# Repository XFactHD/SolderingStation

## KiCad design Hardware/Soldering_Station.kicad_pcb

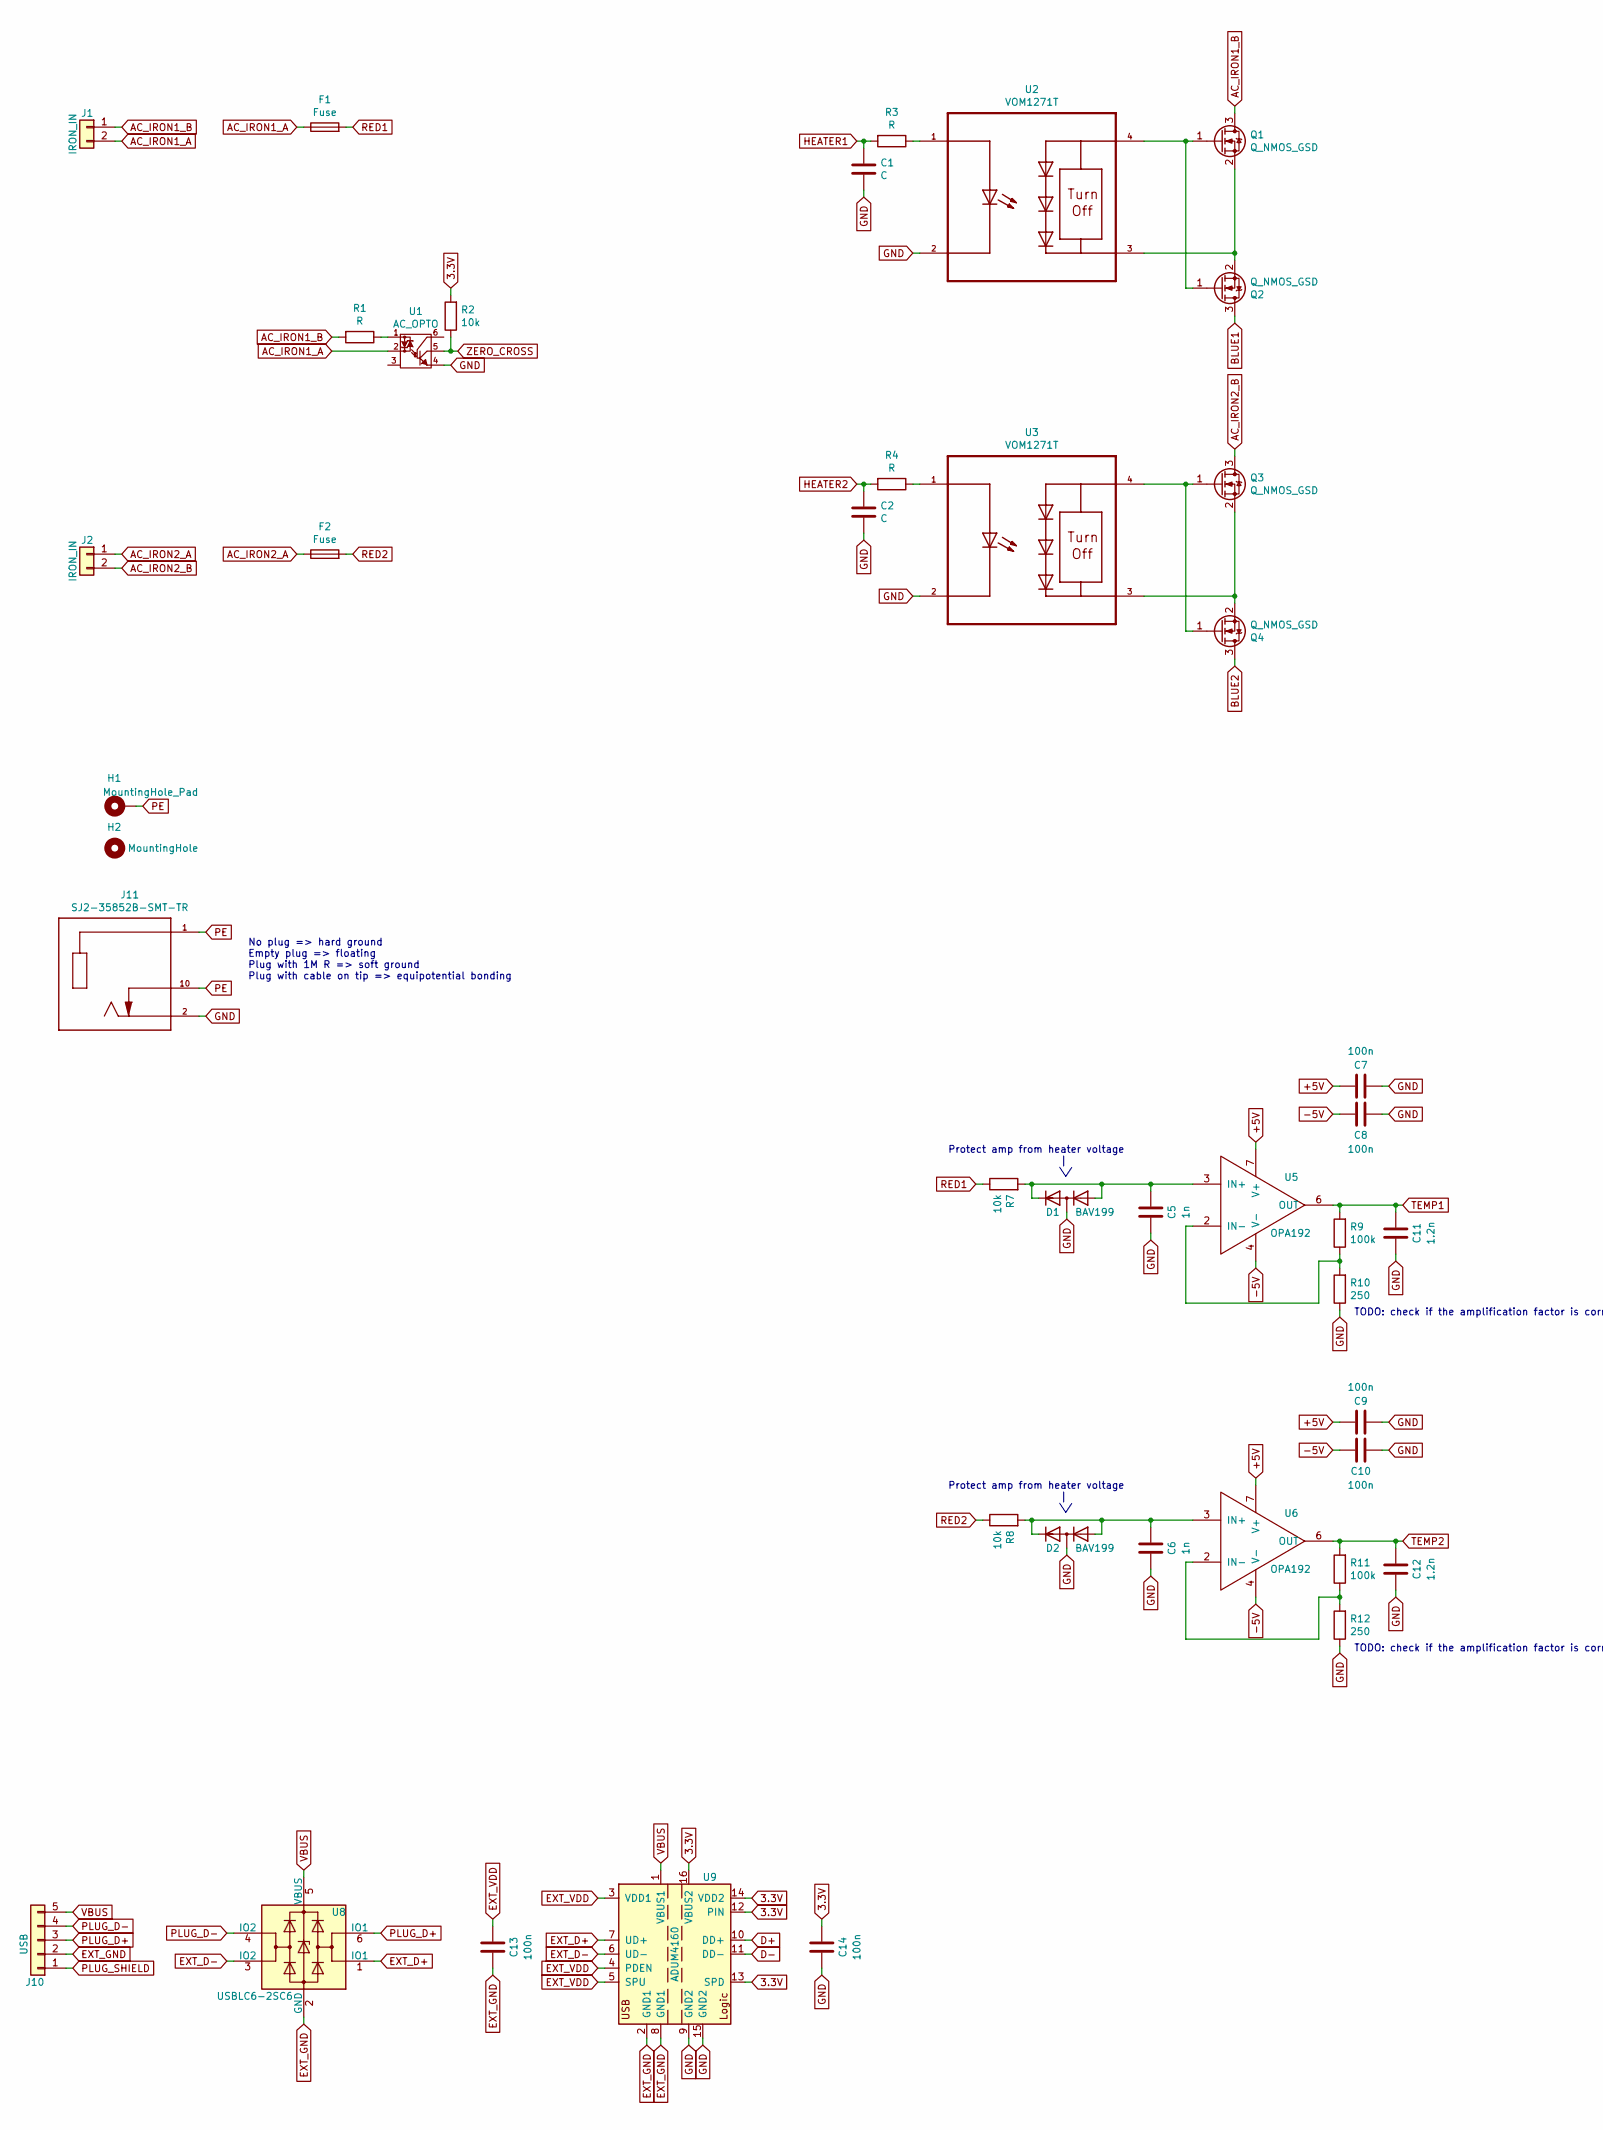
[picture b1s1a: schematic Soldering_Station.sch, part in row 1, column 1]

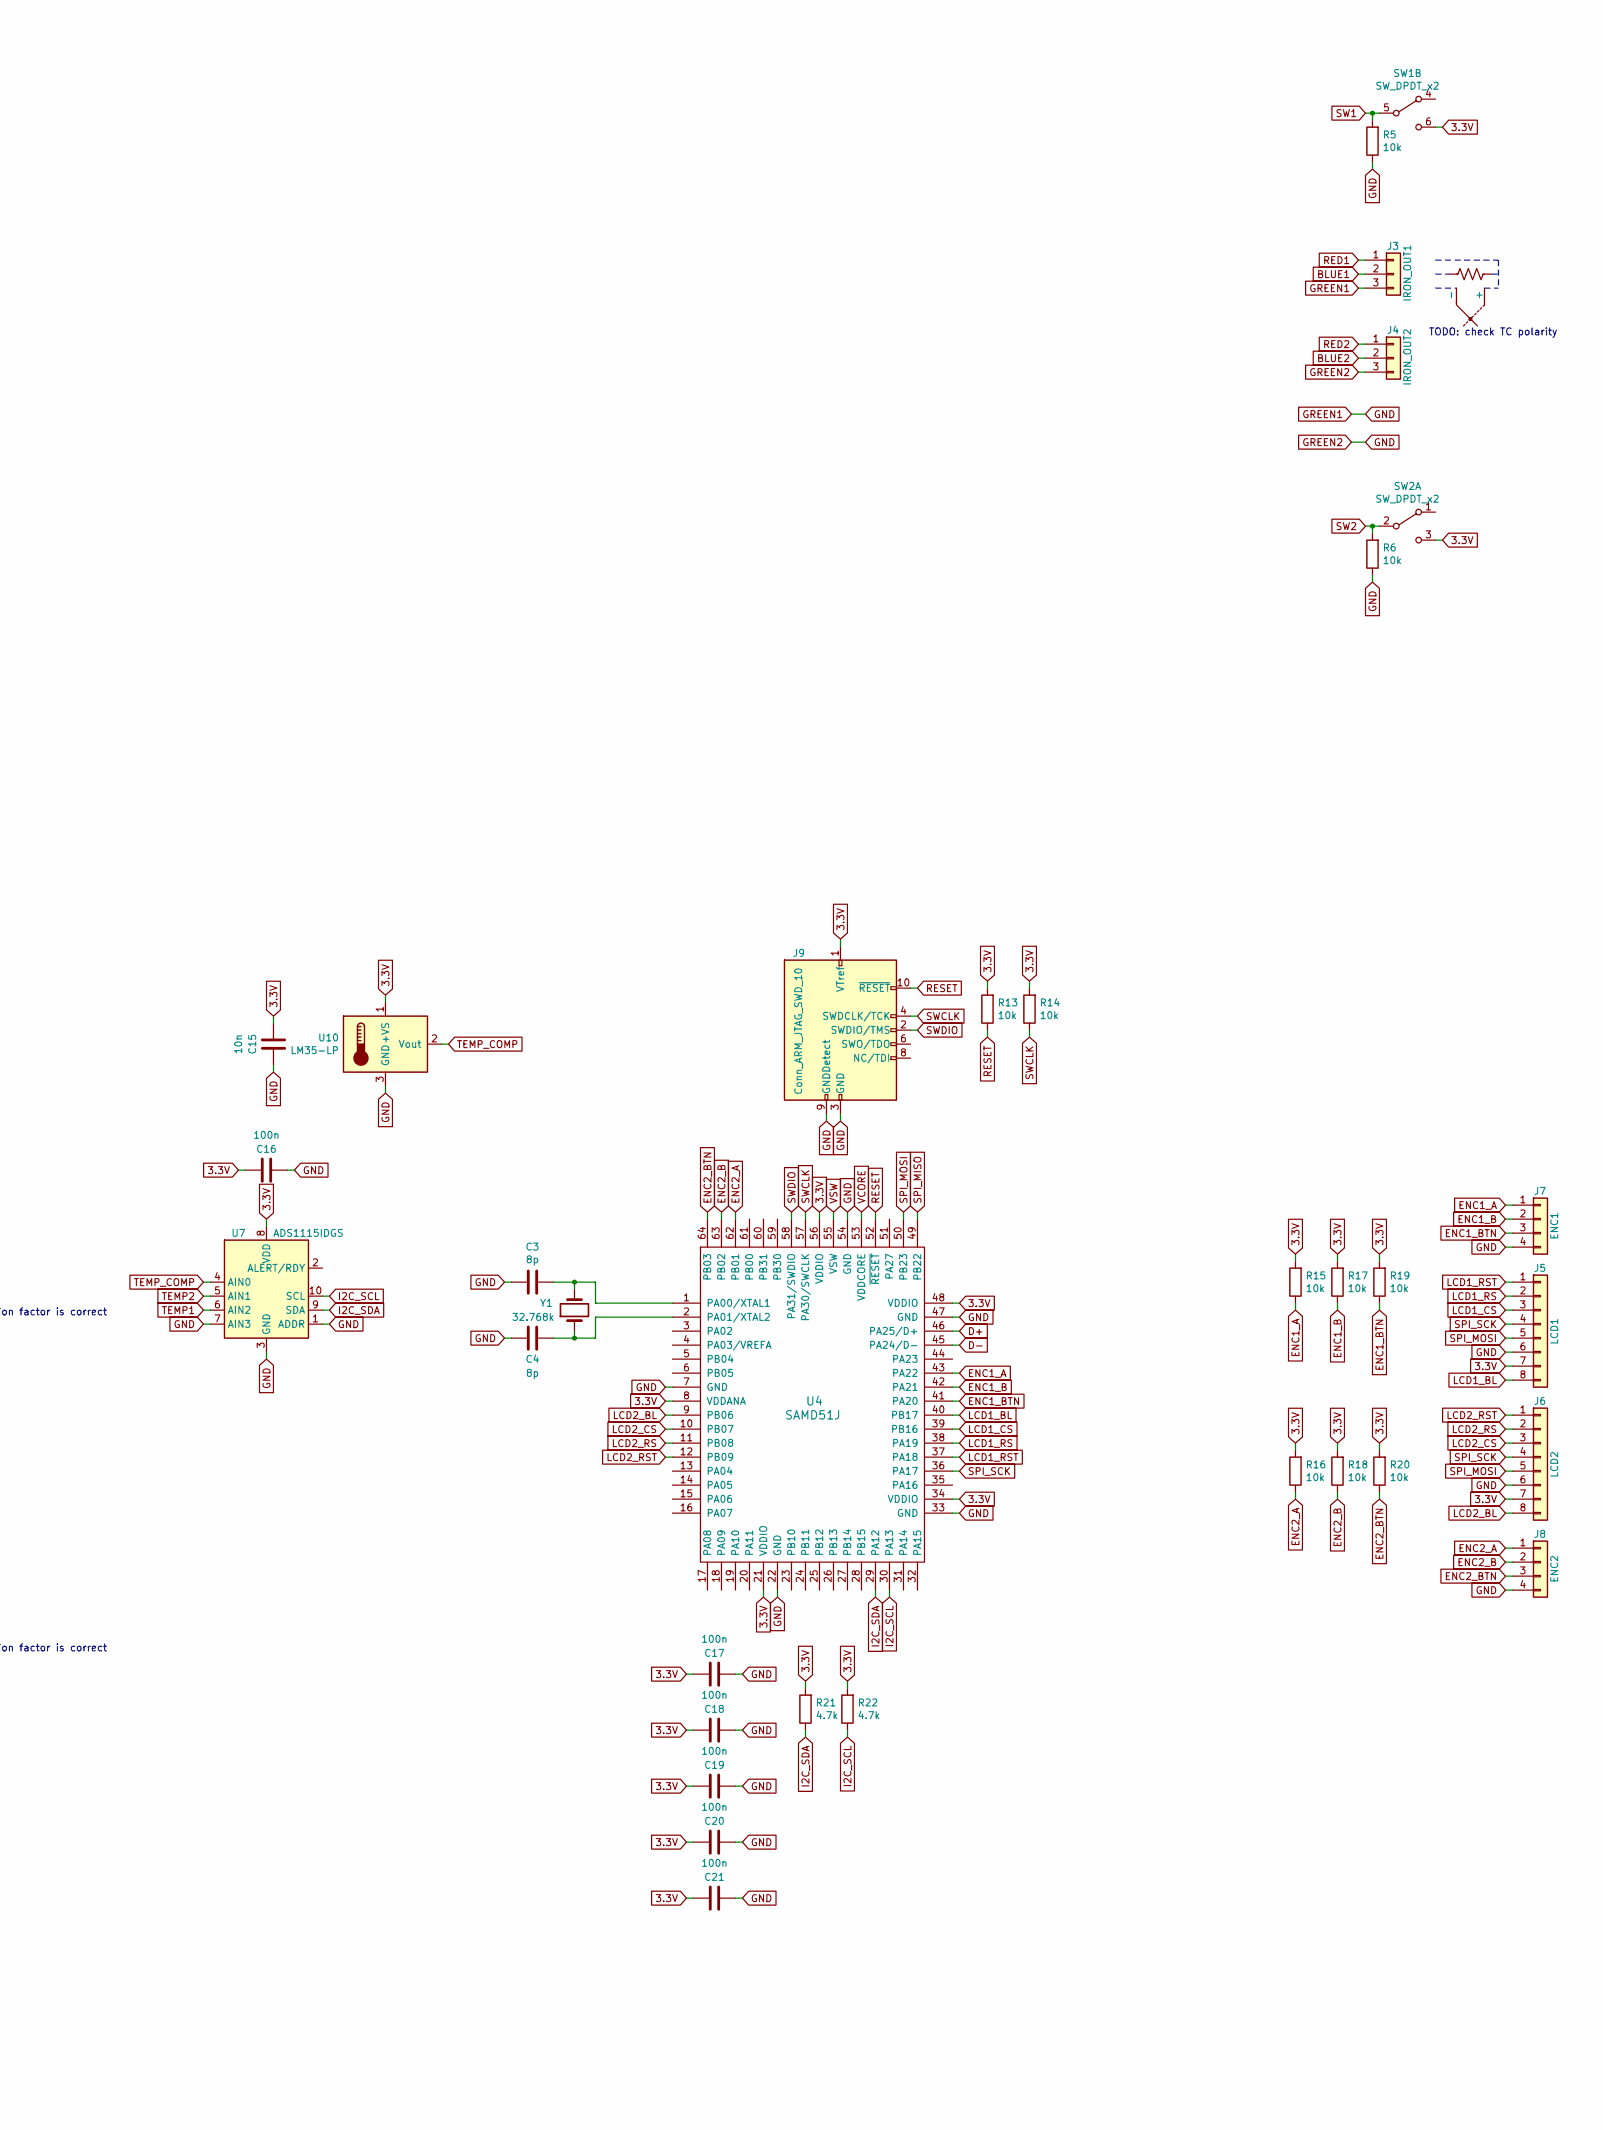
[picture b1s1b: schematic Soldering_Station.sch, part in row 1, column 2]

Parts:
C1, C2: C; C_0805
C3, C4: 8p; C_0805
C5, C6: 1n; C_0805
C7, C8, C9, C10, C13, C14, C16, C17, C18, C19, C20, C21: 100n; C_0805
C11, C12: 1.2n; C_0805
C15: 10n; C_0805
D1, D2: BAV199; SOT-23
F1, F2: Fuse; Fuseholder5x20_horiz_open_universal_Type-III
H1: MountingHole_Pad; 1pin
H2: MountingHole; 1pin
J1, J2: IRON_IN; PhoenixContact_MSTBVA-G_02x5.08mm_Vertical
J3: IRON_OUT1; PhoenixContact_MSTBVA-G_03x5.08mm_Vertical
J4: IRON_OUT2; PhoenixContact_MSTBVA-G_03x5.08mm_Vertical
J5: LCD1; JST_PH_B8B-PH-K_08x2.00mm_Straight
J6: LCD2; JST_PH_B8B-PH-K_08x2.00mm_Straight
J7: ENC1; JST_PH_B4B-PH-K_04x2.00mm_Straight
J8: ENC2; JST_PH_B4B-PH-K_04x2.00mm_Straight
J9: Conn_ARM_JTAG_SWD_10; Pin_Header_Straight_2x05_Pitch1.27mm
J10: USB; Pin_Header_Angled_1x05_Pitch2.54mm
J11: SJ2-35852B-SMT-TR; CUI_SJ2-35852B-SMT-TR
Q1, Q2, Q3, Q4: Q_NMOS_GSD; Infineon_PG-HSOF-8-1_ThermalVias
R1, R3, R4: R; R_0805
R2, R5, R6, R7, R8, R13, R14, R15, R16, R17, R18, R19, R20: 10k; R_0805
R9, R11: 100k; R_0805
R10, R12: 250; R_0805
R21, R22: 4.7k; R_0805
R130000: R_US
SW1, SW2: SW_DPDT_x2; NE182AEESNP6AMP
TC1: Thermocouple
U1: AC_OPTO; DIP-6_W7.62mm_SMDSocket_SmallPads
U2, U3: VOM1271T; SOP-4_3.8x4.1mm_Pitch2.54mm
U4: SAMD51J; TQFP-64_10x10mm_Pitch0.5mm
U5, U6: OPA192; SOIC-8_3.9x4.9mm_Pitch1.27mm
U7: ADS1115IDGS; TSSOP-10_3x3mm_Pitch0.5mm
U8: USBLC6-2SC6; SOT-23-6
U9: ADUM4160; SOIC-16W_7.5x10.3mm_Pitch1.27mm
U10: LM35-LP; TO-92_Inline_Narrow_Oval
Y1: 32.768k; Crystal_SMD_MicroCrystal_CC5V-T1A-2pin_4.1x1.5mm

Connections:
3.3V: C14.2, C15.1, C16.2, C17.2, C18.2, C19.2, C20.2, C21.2, J5.7, J6.7, J9.1 (VTref), R2.2, R13.2, R14.2, R15.2, R16.2, R17.2, R18.2, R19.2, R20.2, R21.2, R22.2, SW1.6 (C), SW2.3 (C), U4.8 (VDDANA), U4.21 (VDDIO), U4.34 (VDDIO), U4.48 (VDDIO), U4.56 (VDDIO), U7.8 (VDD), U9.12 (PIN), U9.13 (SPD), U9.14 (VDD2), U9.16 (VBUS2), U10.1 (+VS)
+5V: C7.2, C9.2, U5.7 (V+), U6.7 (V+)
-5V: C8.1, C10.1, U5.4 (V-), U6.4 (V-)
AC_IRON1_A: F1.1, J1.2, U1.2 (IN_2)
AC_IRON1_B: J1.1, Q1.3 (D), R1.2
AC_IRON2_A: F2.1, J2.1
AC_IRON2_B: J2.2, Q3.3 (D)
BLUE1: J3.2, Q2.3 (D)
BLUE2: J4.2, Q4.3 (D)
D+: U4.46 (PA25/D+), U9.10 (DD+)
D-: U4.45 (PA24/D-), U9.11 (DD-)
ENC1_A: J7.1, R15.1, U4.43 (PA22)
ENC1_B: J7.2, R17.1, U4.42 (PA21)
ENC1_BTN: J7.3, R19.1, U4.41 (PA20)
ENC2_A: J8.1, R16.1, U4.62 (PB01)
ENC2_B: J8.2, R18.1, U4.63 (PB02)
ENC2_BTN: J8.3, R20.1, U4.64 (PB03)
EXT_D+: U8.1 (IO1), U9.7 (UD+)
EXT_D-: U8.3 (IO2), U9.6 (UD-)
EXT_GND: C13.1, J10.2, U8.2 (GND), U9.2 (GND1), U9.8 (GND1)
EXT_VDD: C13.2, U9.3 (VDD1), U9.4 (PDEN), U9.5 (SPU)
GND: C1.2, C2.2, C3.1, C4.1, C5.1, C6.1, C7.1, C8.2, C9.1, C10.2, C11.1, C12.1, C14.1, C15.2, C16.1, C17.1, C18.1, C19.1, C20.1, C21.1, D1.3 (AC), D2.3 (AC), J3.3, J4.3, J5.6, J6.6, J7.4, J8.4, J9.3 (GND), J9.5 (GND), J9.9 (GNDDetect), J11.2 (TIP), R5.1, R6.1, R10.1, R12.1, U1.4 (E), U2.2 (C1), U3.2 (C1), U4.7 (GND), U4.22 (GND), U4.33 (GND), U4.47 (GND), U4.54 (GND), U7.1 (ADDR), U7.3 (GND), U7.7 (AIN3), U9.9 (GND2), U9.15 (GND2), U10.3 (GND)
HEATER1: C1.1, R3.2
HEATER2: C2.1, R4.2
I2C_SCL: R22.1, U4.30 (PA13), U7.10 (SCL)
I2C_SDA: R21.1, U4.29 (PA12), U7.9 (SDA)
LCD1_BL: J5.8, U4.40 (PB17)
LCD1_CS: J5.3, U4.39 (PB16)
LCD1_RS: J5.2, U4.38 (PA19)
LCD1_RST: J5.1, U4.37 (PA18)
LCD2_BL: J6.8, U4.9 (PB06)
LCD2_CS: J6.3, U4.10 (PB07)
LCD2_RS: J6.2, U4.11 (PB08)
LCD2_RST: J6.1, U4.12 (PB09)
unnamed: C3.2, U4.1 (PA00/XTAL1), Y1.2
unnamed: C4.2, U4.2 (PA01/XTAL2), Y1.1
unnamed: C5.2, D1.1 (A), D1.2 (C), R7.2, U5.3 (IN+)
unnamed: C6.2, D2.1 (A), D2.2 (C), R8.2, U6.3 (IN+)
unnamed: Q1.1 (G), Q2.1 (G), U2.4 (A2)
unnamed: Q1.2 (S), Q2.2 (S), U2.3 (C2)
unnamed: Q3.1 (G), Q4.1 (G), U3.4 (A2)
unnamed: Q3.2 (S), Q4.2 (S), U3.3 (C2)
unnamed: R1.1, U1.1 (IN_1)
unnamed: R3.1, U2.1 (A1)
unnamed: R4.1, U3.1 (A1)
unnamed: R9.1, R10.2, U5.2 (IN-)
unnamed: R11.1, R12.2, U6.2 (IN-)
PE: H1.1, J11.1 (SLEEVE), J11.10 (TIP_SWITCH)
PLUG_D+: J10.3, U8.6 (IO1)
PLUG_D-: J10.4, U8.4 (IO2)
PLUG_SHIELD: J10.1
RED1: F1.2, J3.1, R7.1
RED2: F2.2, J4.1, R8.1
RESET: J9.10 (~RESET~), R13.1, U4.52 (~RESET)
SPI_MISO: U4.49 (PB22)
SPI_MOSI: J5.5, J6.5, U4.50 (PB23)
SPI_SCK: J5.4, J6.4, U4.36 (PA17)
SW1: R5.2, SW1.5 (B)
SW2: R6.2, SW2.2 (B)
SWCLK: J9.4 (SWDCLK/TCK), R14.1, U4.57 (PA30/SWCLK)
SWDIO: J9.2 (SWDIO/TMS), U4.58 (PA31/SWDIO)
TEMP1: C11.2, R9.2, U5.6 (OUT), U7.6 (AIN2)
TEMP2: C12.2, R11.2, U6.6 (OUT), U7.5 (AIN1)
TEMP_COMP: U7.4 (AIN0), U10.2 (Vout)
VBUS: J10.5, U8.5 (VBUS), U9.1 (VBUS1)
VCORE: U4.53 (VDDCORE)
VSW: U4.55 (VSW)
ZERO_CROSS: R2.1, U1.5 (C)

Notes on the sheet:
No plug => hard ground Empty plug => floating Plug with 1M R => soft ground Plug with cable on tip => equipotential bonding
TODO: check TC polarity
TODO: check if the amplification factor is correct
Protect amp from heater voltage | \/

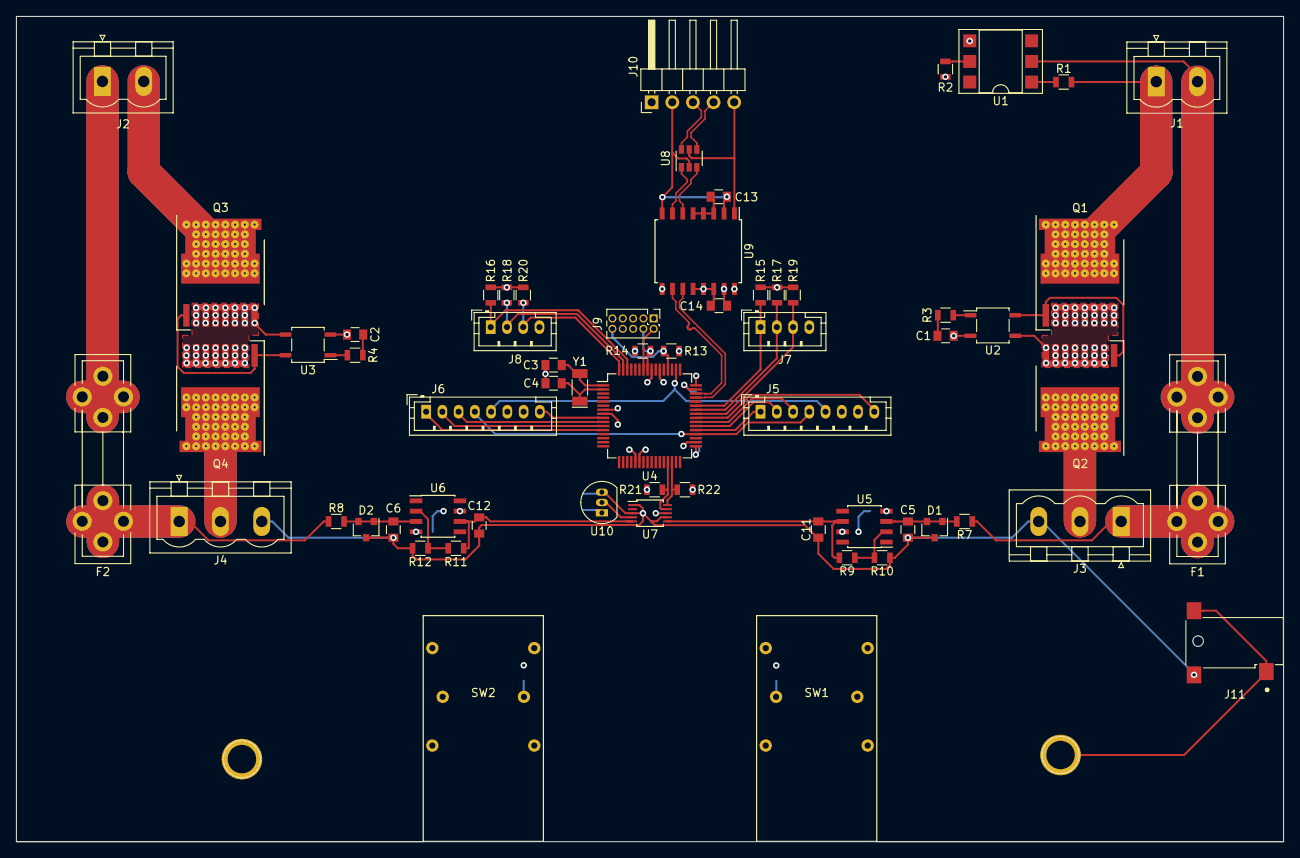
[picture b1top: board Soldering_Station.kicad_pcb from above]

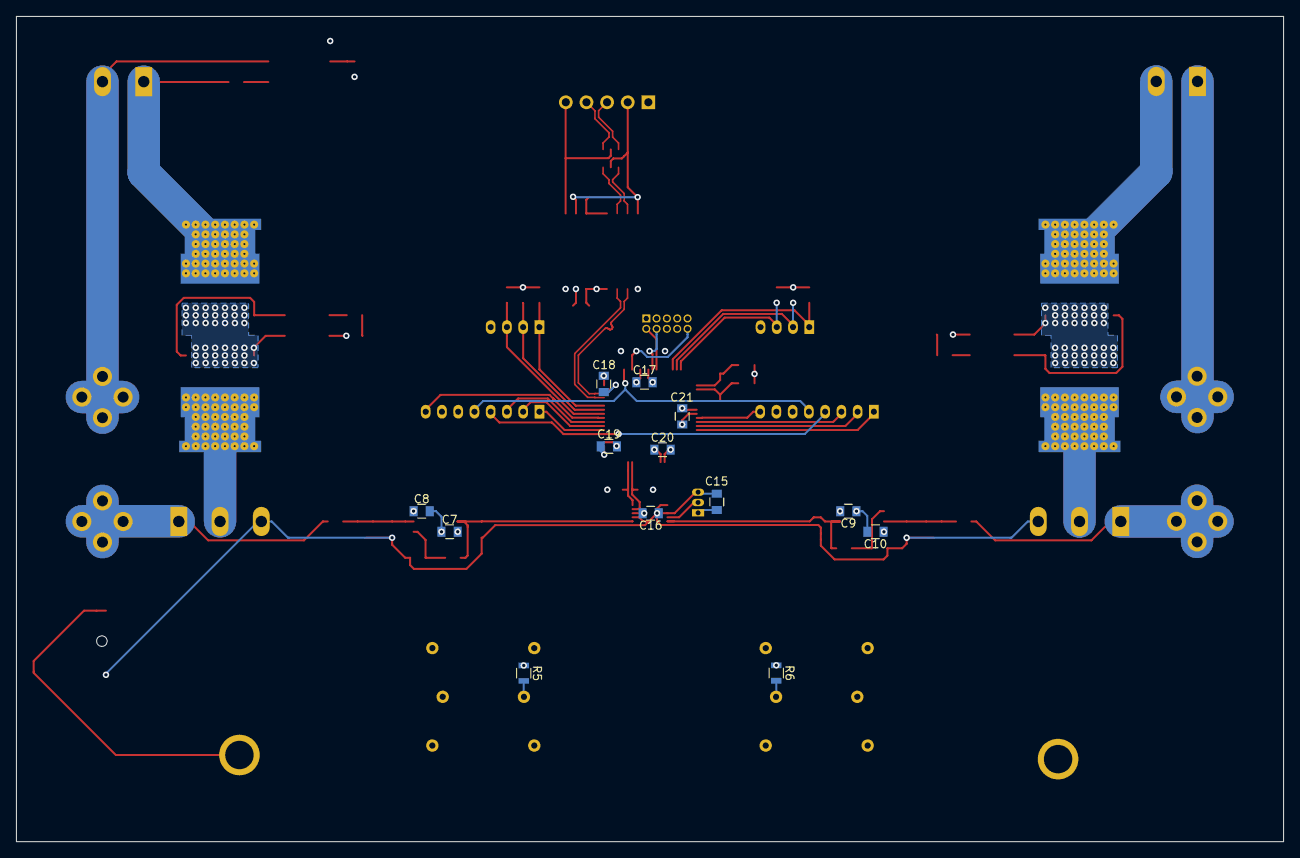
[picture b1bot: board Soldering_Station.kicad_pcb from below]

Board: 4 copper layers, 156.0 x 101.6 mm, 77 parts (13 on the bottom side), 64 nets.
